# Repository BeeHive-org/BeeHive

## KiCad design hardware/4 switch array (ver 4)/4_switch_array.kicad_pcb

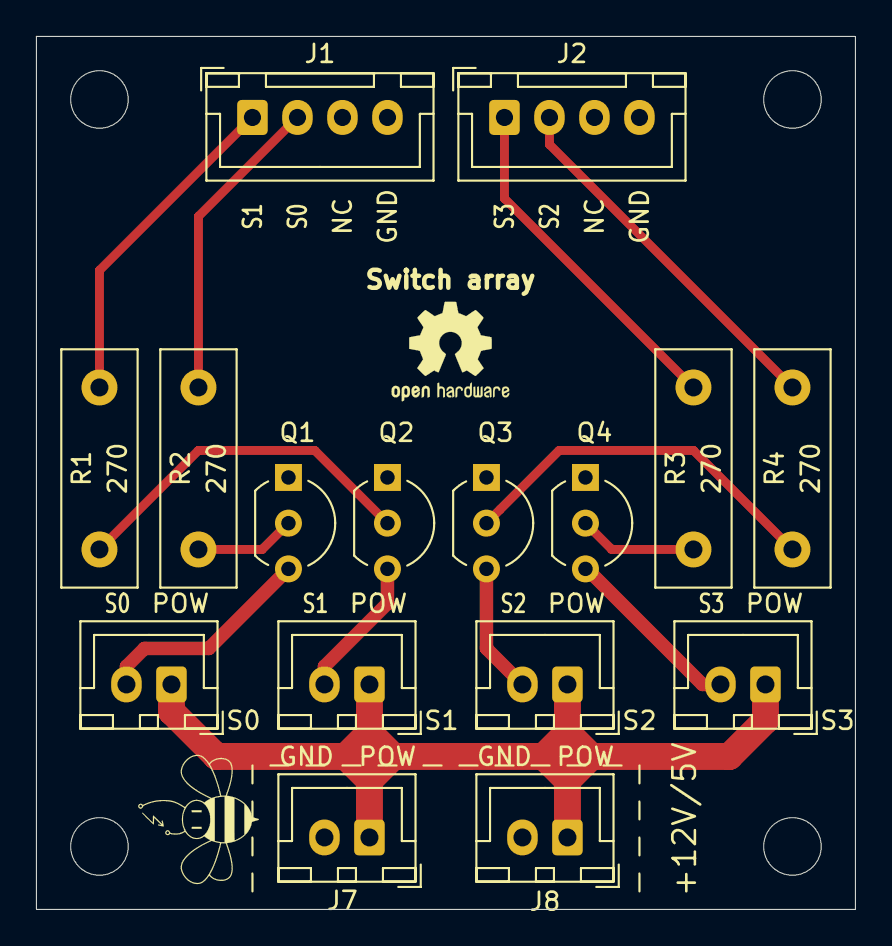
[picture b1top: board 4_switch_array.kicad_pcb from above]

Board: 2 copper layers, 45.5 x 48.5 mm, 16 parts (0 on the bottom side), 14 nets.

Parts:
J1, J2: Conn_01x04; JST_XH_B4B-XH-A_1x04_P2.50mm_Vertical
J3, J4, J5, J6, J7, J8: Conn_01x02; JST_XH_B2B-XH-A_1x02_P2.50mm_Vertical
Q1, Q2, Q3, Q4: Q_NPN_EBC; TO-92_Inline_Wide
R1, R2, R3, R4: 270; R_Box_L13.0mm_W4.0mm_P9.00mm

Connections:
+12V: J3.1, J4.1, J5.1, J6.1, J7.1, J8.1
GND: J1.4, J2.4, J7.2, J8.2, Q1.1, Q2.1, Q3.1, Q4.1
unnamed: J3.2, Q1.3
unnamed: J4.2, Q2.3
unnamed: J5.2, Q3.3
unnamed: J6.2, Q4.3
unnamed: Q1.2, R2.2
unnamed: Q2.2, R1.2
unnamed: Q3.2, R4.2
unnamed: Q4.2, R3.2
OUT_0: J1.2, R2.1
OUT_1: J1.1, R1.1
OUT_2: J2.1, R3.1
OUT_3: J2.2, R4.1

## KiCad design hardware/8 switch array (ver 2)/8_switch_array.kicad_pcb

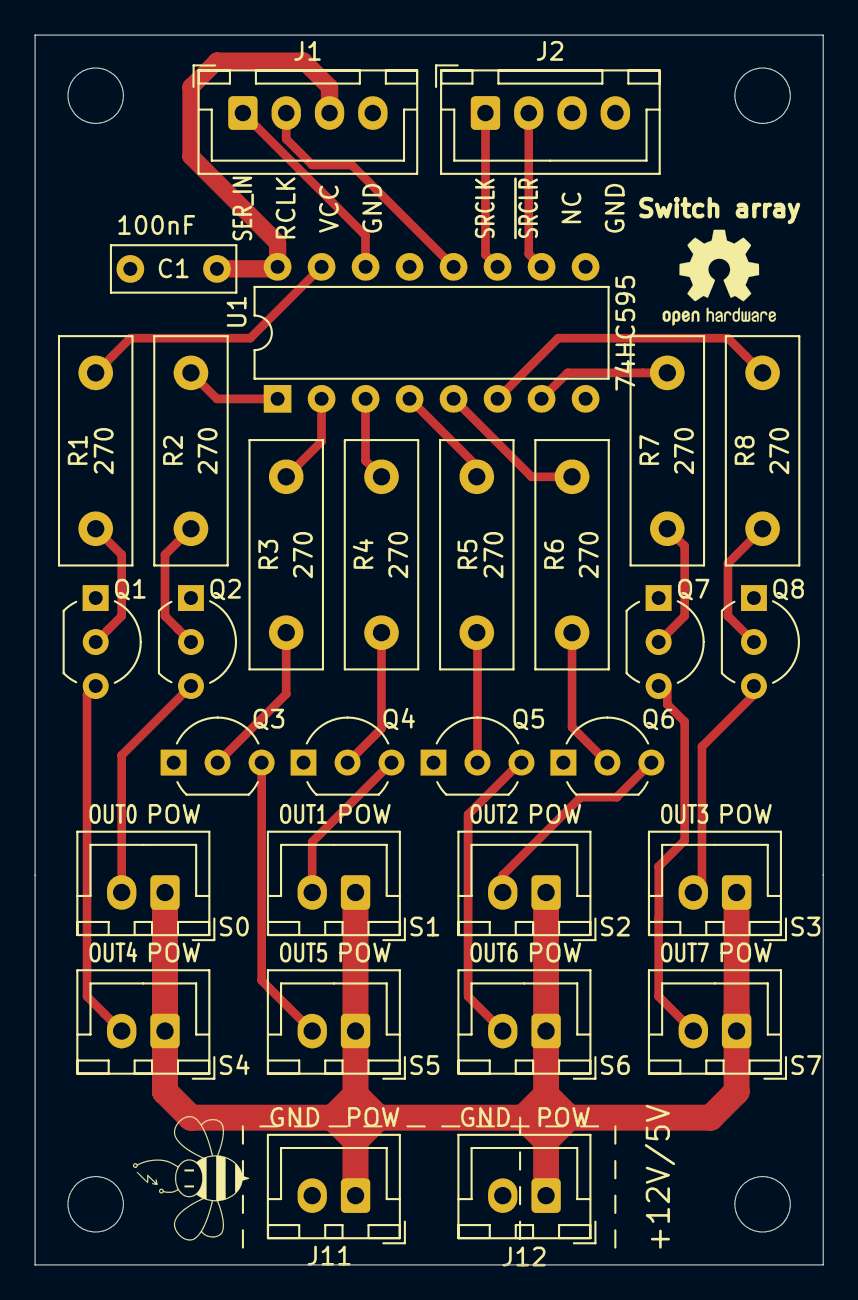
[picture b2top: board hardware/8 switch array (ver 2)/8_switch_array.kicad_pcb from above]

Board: 2 copper layers, 45.5 x 71.0 mm, 30 parts (0 on the bottom side), 31 nets.

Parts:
C1: 100nF; C_Disc_D7.0mm_W2.5mm_P5.00mm
J1, J2: Conn_01x04; JST_XH_B4B-XH-A_1x04_P2.50mm_Vertical
J3, J4, J5, J6, J7, J8, J9, J10, J11, J12: Conn_01x02; JST_XH_B2B-XH-A_1x02_P2.50mm_Vertical
Q1, Q2, Q3, Q4, Q5, Q6, Q7, Q8: Q_NPN_EBC; TO-92_Inline_Wide
R1, R2, R3, R4, R5, R6, R7, R8: 270; R_Box_L13.0mm_W4.0mm_P9.00mm
U1: 74HC595; DIP-16_W7.62mm

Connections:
+5V: C1.1, J1.3, U1.16
+12V: J3.1, J4.1, J5.1, J6.1, J7.1, J8.1, J9.1, J10.1, J11.1, J12.1
GND: C1.2, J1.4, J2.4, J11.2, J12.2, Q1.1, Q2.1, Q3.1, Q4.1, Q5.1, Q6.1, Q7.1, Q8.1, U1.8, U1.9, U1.13
unnamed: J3.2, Q2.3
unnamed: J4.2, Q4.3
unnamed: J5.2, Q6.3
unnamed: J6.2, Q8.3
unnamed: J7.2, Q1.3
unnamed: J8.2, Q3.3
unnamed: J9.2, Q5.3
unnamed: J10.2, Q7.3
unnamed: Q1.2, R1.2
unnamed: Q2.2, R2.2
unnamed: Q3.2, R3.2
unnamed: Q4.2, R4.2
unnamed: Q5.2, R5.2
unnamed: Q6.2, R6.2
unnamed: Q7.2, R7.2
unnamed: Q8.2, R8.2
OUT_0: R1.1, U1.15
OUT_1: R2.1, U1.1
OUT_2: R3.1, U1.2
OUT_3: R4.1, U1.3
OUT_4: R5.1, U1.4
OUT_5: R6.1, U1.5
OUT_6: R7.1, U1.7
OUT_7: R8.1, U1.6
RCLK: J1.2, U1.12
SER_IN: J1.1, U1.14
SRCLK: J2.1, U1.11
SRCLR: J2.2, U1.10

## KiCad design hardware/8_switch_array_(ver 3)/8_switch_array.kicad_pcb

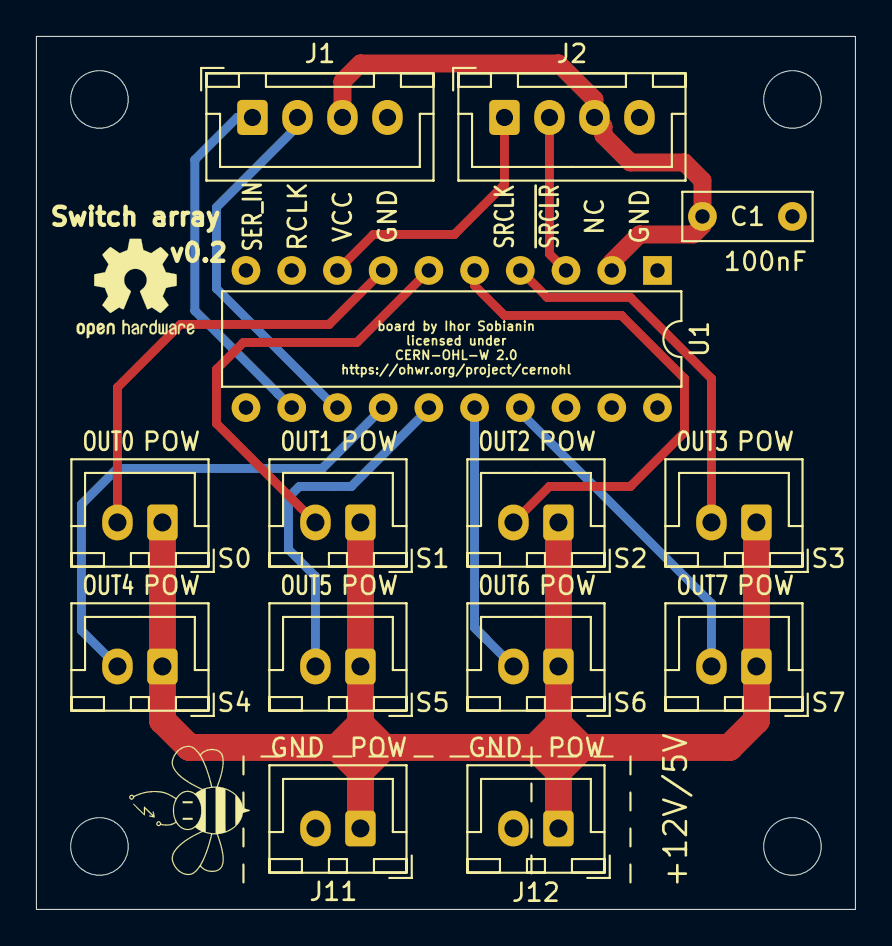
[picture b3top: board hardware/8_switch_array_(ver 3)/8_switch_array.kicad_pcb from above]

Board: 2 copper layers, 45.5 x 48.5 mm, 14 parts (0 on the bottom side), 15 nets.

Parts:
C1: 100nF; C_Disc_D7.0mm_W2.5mm_P5.00mm
J1, J2: Conn_01x04; JST_XH_B4B-XH-A_1x04_P2.50mm_Vertical
J3, J4, J5, J6, J7, J8, J9, J10, J11, J12: Conn_01x02; JST_XH_B2B-XH-A_1x02_P2.50mm_Vertical
U1: TPIC6595; DIP-20_W7.62mm

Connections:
+5V: C1.1, J1.3, J2.3, U1.2
+12V: J3.1, J4.1, J5.1, J6.1, J7.1, J8.1, J9.1, J10.1, J11.1, J12.1
GND: C1.2, J1.4, J2.4, J11.2, J12.2, U1.1, U1.9, U1.10, U1.11, U1.19, U1.20
OUT_0: J6.2, U1.4
OUT_1: J5.2, U1.5
OUT_2: J4.2, U1.6
OUT_3: J3.2, U1.7
OUT_4: J7.2, U1.14
OUT_5: J8.2, U1.15
OUT_6: J10.2, U1.17
OUT_7: J9.2, U1.16
RCLK: J1.1, U1.12
SER_IN: J2.2, U1.3
SRCLK: J1.2, U1.13
SRCLR: J2.1, U1.8

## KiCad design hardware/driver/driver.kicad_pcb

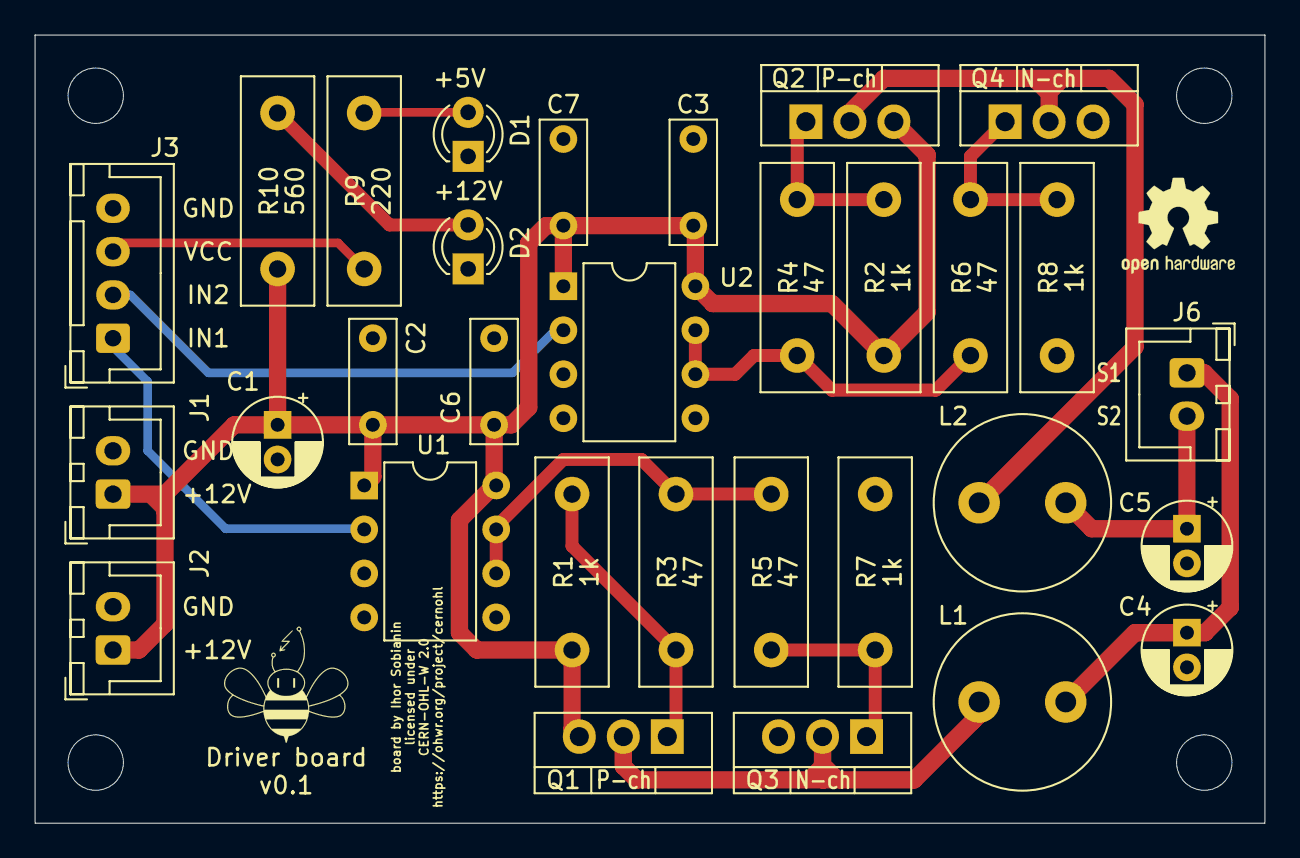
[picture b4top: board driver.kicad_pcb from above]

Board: 2 copper layers, 71.0 x 45.5 mm, 31 parts (0 on the bottom side), 17 nets.

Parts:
C1, C4, C5: 22u; CP_Radial_D5.0mm_P2.00mm
C2, C3, C6, C7: 100nF; C_Disc_D7.0mm_W2.5mm_P5.00mm
D1, D2: LED; LED_D3.0mm
J1, J2, J6: Conn_01x02; JST_XH_B2B-XH-A_1x02_P2.50mm_Vertical
J3: Conn_01x04; JST_XH_B4B-XH-A_1x04_P2.50mm_Vertical
L1, L2: 33u; L_Radial_D10.0mm_P5.00mm_Neosid_SD12_style3
Q1, Q2: IRF9Z34NPBF; TO-220-3_Vertical
Q3, Q4: IRFZ24NPBF; TO-220-3_Vertical
R1, R2, R7, R8: 1k; R_Box_L13.0mm_W4.0mm_P9.00mm
R3, R4, R5, R6: 47; R_Box_L13.0mm_W4.0mm_P9.00mm
R9: 220; R_Box_L13.0mm_W4.0mm_P9.00mm
R10: 560; R_Box_L13.0mm_W4.0mm_P9.00mm
U1, U2: TC4420CPA; DIP-8_W7.62mm

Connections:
+5V: J3.3, R9.1
+12V: C1.1, C2.1, C3.1, C6.1, C7.1, J1.1, J2.1, Q1.3, Q2.3, R1.2, R2.2, R10.1, U1.1, U1.8, U2.1, U2.8
GND: C1.2, C2.2, C3.2, C4.2, C5.2, C6.2, C7.2, D1.1, D2.1, J1.2, J2.2, J3.4, Q3.3, Q4.3, R7.1, R8.1, U1.4, U1.5, U2.4, U2.5
IN1: J3.1, U1.2
IN2: J3.2, U2.2
unnamed: C4.1, J6.1, L1.2
unnamed: C5.1, J6.2, L2.2
unnamed: D1.2, R9.2
unnamed: D2.2, R10.2
unnamed: L1.1, Q1.2, Q3.2
unnamed: L2.1, Q2.2, Q4.2
unnamed: Q1.1, R1.1, R3.2
unnamed: Q2.1, R2.1, R4.2
unnamed: Q3.1, R5.2, R7.2
unnamed: Q4.1, R6.2, R8.2
unnamed: R3.1, R5.1, U1.6, U1.7
unnamed: R4.1, R6.1, U2.6, U2.7

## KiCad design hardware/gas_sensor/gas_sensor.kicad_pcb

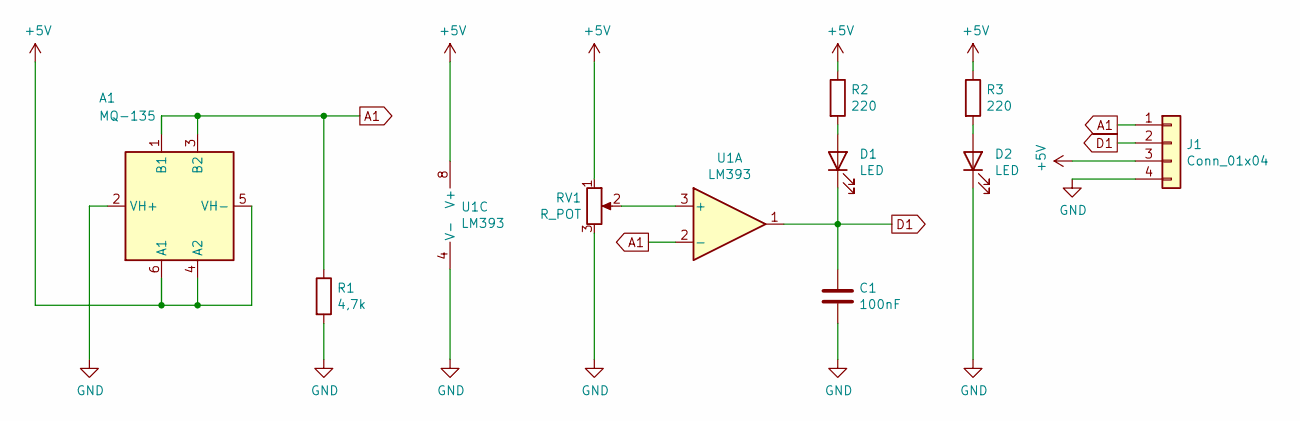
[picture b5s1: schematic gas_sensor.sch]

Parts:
A1: MQ-135; MQ-6
C1: 100nF; C_Disc_D7.0mm_W2.5mm_P5.00mm
D1, D2: LED; LED_D3.0mm
J1: Conn_01x04; JST_XH_B4B-XH-A_1x04_P2.50mm_Vertical
R1: 4,7k; R_Box_L13.0mm_W4.0mm_P9.00mm
R2, R3: 220; R_Box_L13.0mm_W4.0mm_P9.00mm
RV1: R_POT; TRIM_3362P-1-103
U1: LM393; DIP-8_W7.62mm

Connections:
+5V: A1.4 (A2), A1.5 (VH-), A1.6 (A1), J1.3, R2.1, R3.1, RV1.1, U1.8 (V+)
A1: A1.1 (B1), A1.3 (B2), J1.1, R1.1, U1.2 (-)
D1: C1.1, D1.1 (K), J1.2, U1.1
GND: A1.2 (VH+), C1.2, D2.1 (K), J1.4, R1.2, RV1.3, U1.4 (V-)
unnamed: D1.2 (A), R2.2
unnamed: D2.2 (A), R3.2
unnamed: RV1.2, U1.3 (+)

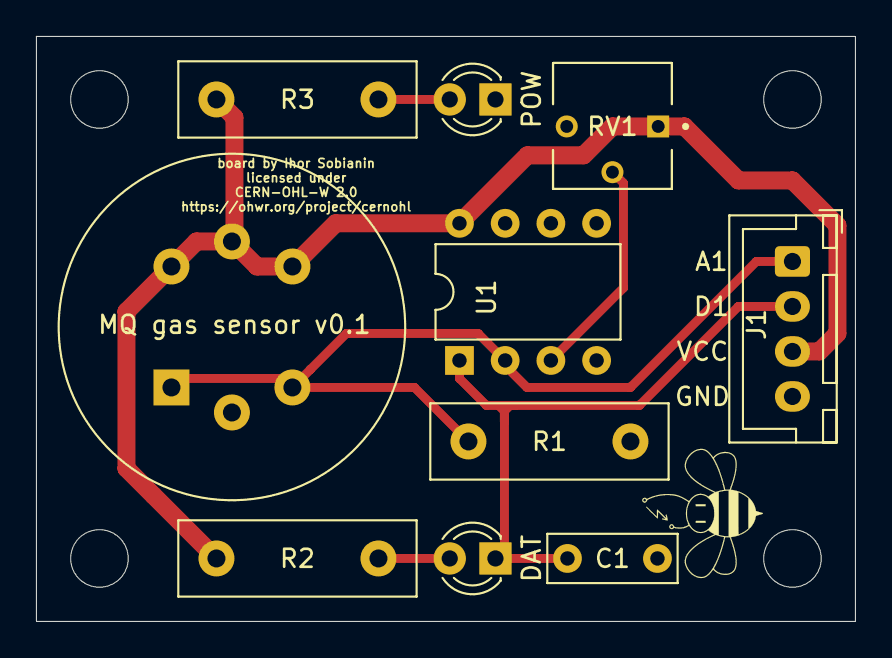
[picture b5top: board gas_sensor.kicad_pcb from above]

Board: 2 copper layers, 45.5 x 32.5 mm, 10 parts (0 on the bottom side), 7 nets.

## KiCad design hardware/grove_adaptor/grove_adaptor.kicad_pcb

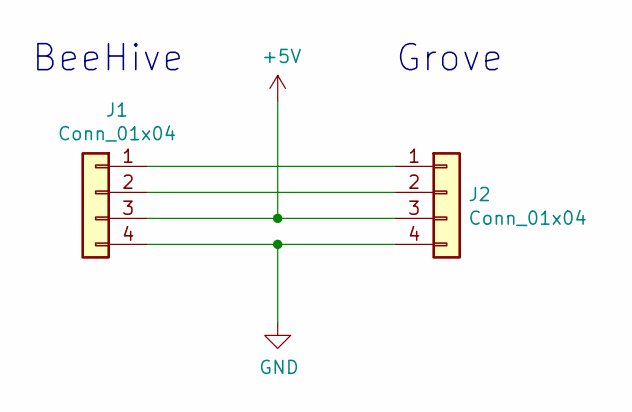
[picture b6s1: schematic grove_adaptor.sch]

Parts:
J1: Conn_01x04; JST_XH_B4B-XH-A_1x04_P2.50mm_Vertical
J2: Conn_01x04; 4P-LEADED-2.0

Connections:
+5V: J1.3, J2.3
GND: J1.4, J2.4
unnamed: J1.1, J2.1
unnamed: J1.2, J2.2

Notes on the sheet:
BeeHive
Grove

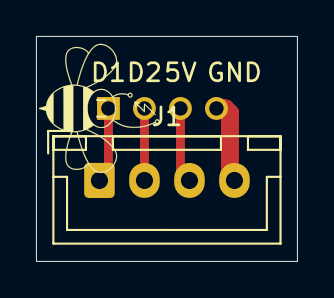
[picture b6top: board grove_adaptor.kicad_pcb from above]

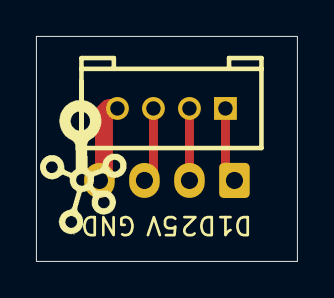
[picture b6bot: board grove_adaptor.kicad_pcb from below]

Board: 2 copper layers, 14.5 x 12.5 mm, 3 parts (2 on the bottom side), 4 nets.

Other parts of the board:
U$3: TWIGLOGO

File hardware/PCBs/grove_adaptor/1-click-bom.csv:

References,Qty,Description,Manufacturer,MPN,Manufacturer,MPN,Manufacturer,MPN,Manufacturer,MPN,Manufacturer,MPN,Digikey,Mouser,RS,Newark,Farnell
J1,1,CONN HEADER XH TOP 4POS 2.5MM,JST,B4B-XH-A (LF)(SN),,,,,,,,,455-2249-ND,,8201551,,1516278
J2,1,Grove male header,M5Stack Technology Co. Ltd.,A118,,,,,,,,,2221-A118-ND,,,,

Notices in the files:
hardware/8_switch_array_(ver 3)/8_switch_array.kicad_pcb:
licensed under
CERN-OHL-W 2.0
